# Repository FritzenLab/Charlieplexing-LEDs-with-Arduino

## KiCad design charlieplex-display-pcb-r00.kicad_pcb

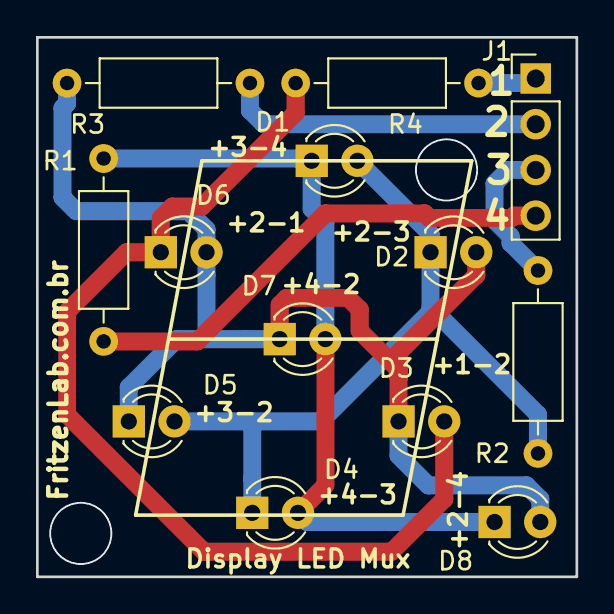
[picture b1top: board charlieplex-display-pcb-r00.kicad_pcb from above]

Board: 2 copper layers, 30.0 x 30.0 mm, 13 parts (0 on the bottom side), 8 nets.

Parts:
D1, D2, D3, D4, D5, D6, D7, D8: LED; LED_D3.0mm
J1: Conn_01x04; PinHeader_1x04_P2.54mm_Vertical
R1, R2, R3, R4: R_US; R_Axial_DIN0207_L6.3mm_D2.5mm_P10.16mm_Horizontal

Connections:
unnamed: D1.1, D4.2, D7.2, D8.1, R1.1
unnamed: D1.2, D2.1, D4.1, D5.2, R2.1
unnamed: D2.2, D3.1, D5.1, D6.2, D7.1, D8.2, R3.1
unnamed: D3.2, D6.1, R4.1
unnamed: J1.1, R4.2
unnamed: J1.2, R3.2
unnamed: J1.3, R2.2
unnamed: J1.4, R1.2

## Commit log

2018-04-07 added schematic and code
    added schematic and code
2018-04-07 added images and video
    added images and video of the charlieplexing hardware+software working
2018-04-07 changd time to 62mS
    changd time to 62mS
2018-04-07 added GIF image of the chalieplexing
    added GIF image of the chalieplexing
2018-04-07 added schematic diagram image
    added schematic diagram image
2019-03-05 criada PCI display LED 7 segmentos
    criada PCI display LED 7 segmentos
